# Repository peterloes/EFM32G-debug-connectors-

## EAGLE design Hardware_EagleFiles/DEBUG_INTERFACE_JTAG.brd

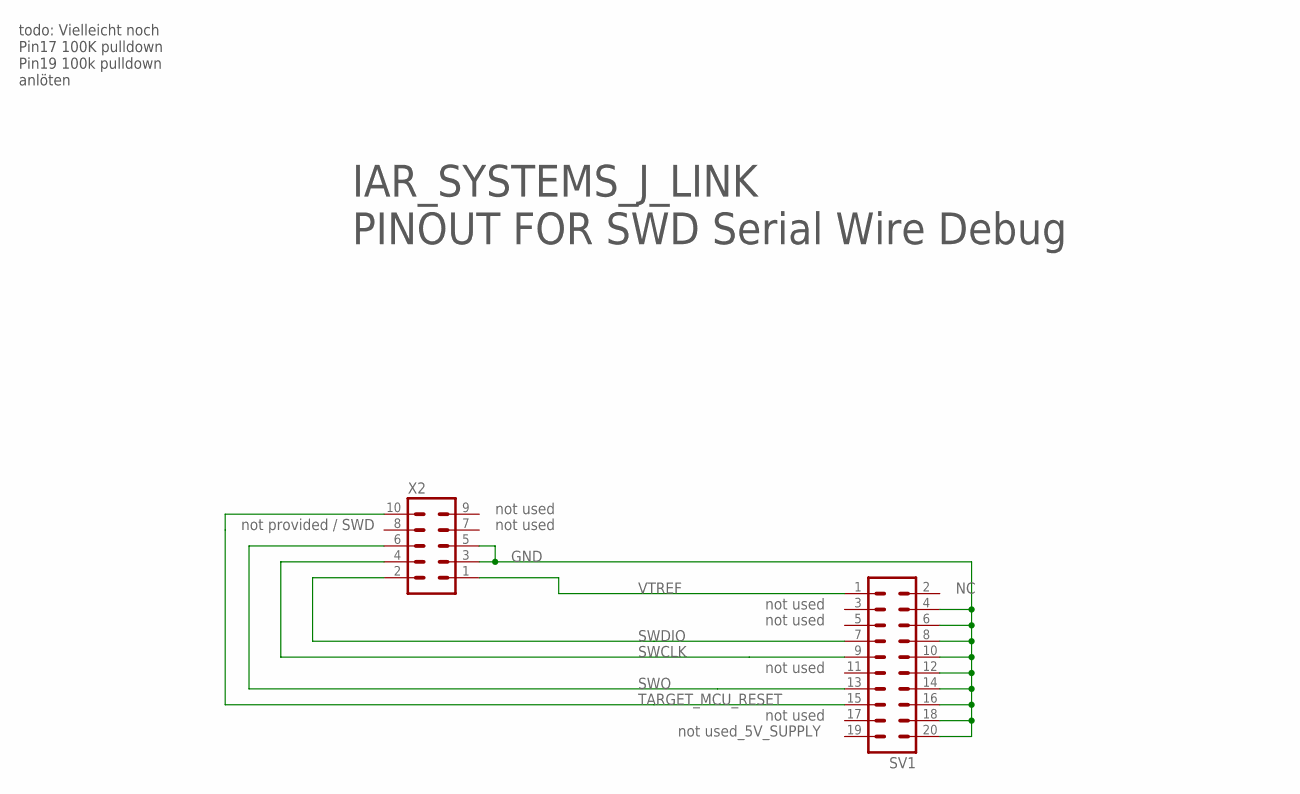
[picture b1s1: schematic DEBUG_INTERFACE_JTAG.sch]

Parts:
SV1: ML20
X2: ML10

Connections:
GND: SV1.4, SV1.6, SV1.8, SV1.10, SV1.12, SV1.14, SV1.16, SV1.18, SV1.20, X2.3, X2.5
SWCLK: SV1.9, X2.4
SWDIO: SV1.7, X2.2
SWO: SV1.13, X2.6
TARGET_MCU_RESET: SV1.15, X2.10
VTREF: SV1.1, X2.1

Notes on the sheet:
not used
not used_5V_SUPPLY
IAR_SYSTEMS_J_LINK PINOUT FOR SWD Serial Wire Debug
not provided / SWD
todo: Vielleicht noch Pin17 100K pulldown Pin19 100k pulldown anlöten

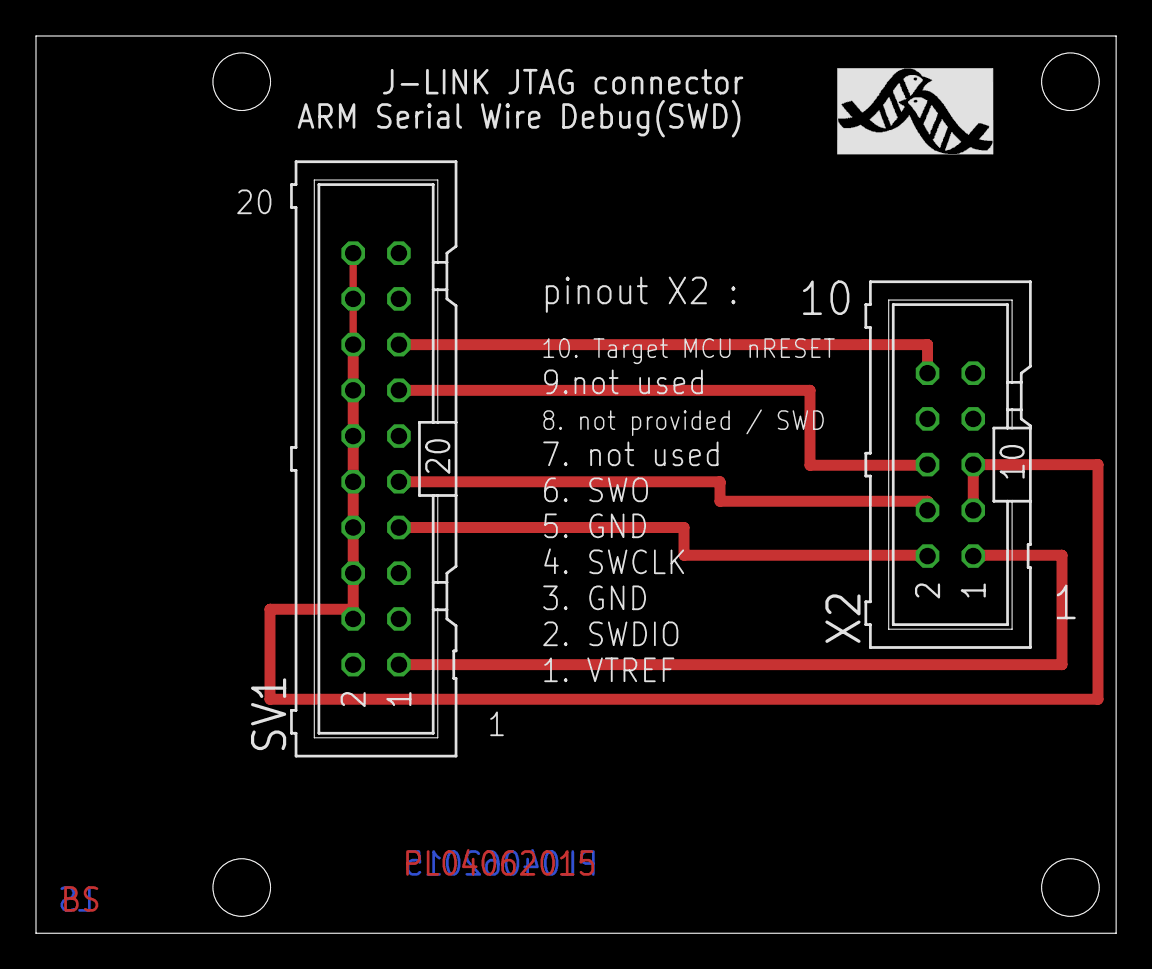
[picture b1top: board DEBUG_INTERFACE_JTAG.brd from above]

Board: 4 copper layers, 60.0 x 49.8 mm, 3 parts (0 on the bottom side), 6 nets.

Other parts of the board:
U$2: MPIO-ICON
